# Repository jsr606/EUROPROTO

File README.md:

# EUROPROTO
an arduino / atmega platform for making digital eurorack modules and
various helper PCBs

based on on the [CHEAP, FAT and OPEN](https://vsionhairies.info/) synthesizer

## a what?
arduino based eurorack module with dual channel DAC output

kind of works :)

this is a prototyping platform. you can make modules that looks like this

## first version for sound days at MPLab
[workshop description and assembly guides here](/SoundDays_MPlab/README.md)

## rev3 board is here now
look in the rev3 folder. it's all old eagle stuff that i can't really open anymore, but it should possibly work?

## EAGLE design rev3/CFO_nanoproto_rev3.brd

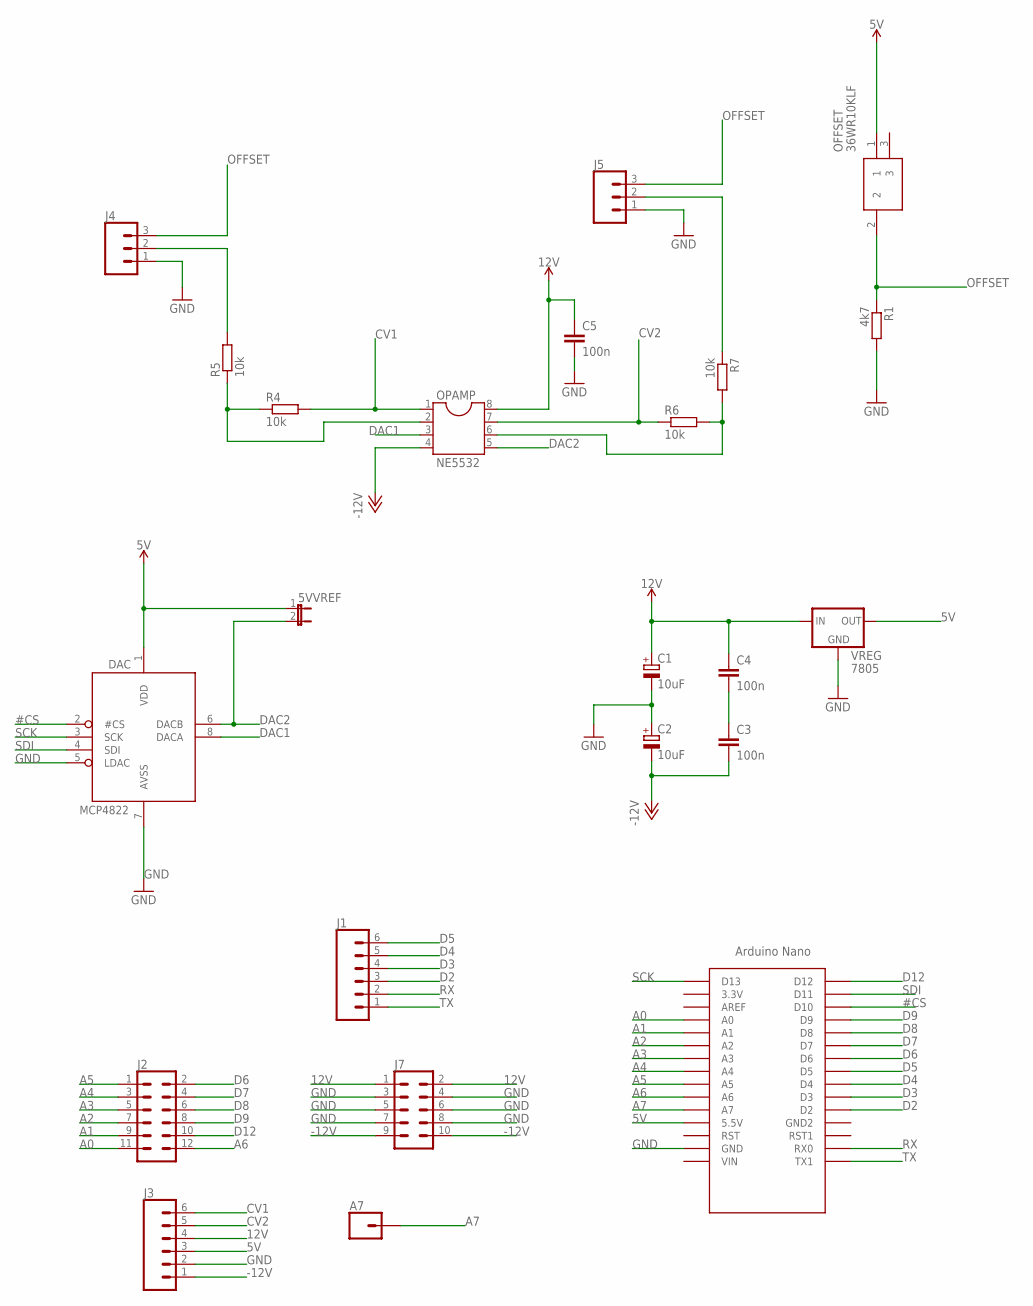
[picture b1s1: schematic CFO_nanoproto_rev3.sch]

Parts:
5VVREF: JUMPER-2PTH; 1X02
A7: CONN_01; 1X01
C1, C2: 10uF; E2-5
C3, C4, C5: 100n; C050-025X075
DAC: MCP4822; DIL08
J1, J3: CONN_06NO_SILK_NO_POP; 1X06_NO_SILK
J2: 2X6 FEMALE; 2X6
J4, J5: CONN_03; 1X03
J7: EURO_CONN_05X2SHD; 2X5-SHROUDED
OFFSET: 36WR10KLF
OPAMP: NE5532; DIL08
R1: 4k7; 0207/10
R4, R5, R6, R7: 10k; 0207/10
U$2: NANO
VREG: 7805; 78XXL_NOHOLE

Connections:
5V: 5VVREF.1, DAC.1 (VDD), J3.3, OFFSET.1, U$2.5V (5.5V), VREG.OUT
12V: C1.+, C4.1, C5.1, J3.4, J7.1, J7.2, OPAMP.8, VREG.IN
#CS: DAC.2 (#CS), U$2.D10
-12V: C2.-, C3.2, J3.1, J7.9, J7.10, OPAMP.4
A0: J2.11, U$2.A0
A1: J2.9, U$2.A1
A2: J2.7, U$2.A2
A3: J2.5, U$2.A3
A4: J2.3, U$2.A4
A5: J2.1, U$2.A5
A6: J2.12, U$2.A6
A7: A7.1, U$2.A7
CV1: J3.6, OPAMP.1, R4.2
CV2: J3.5, OPAMP.7, R6.1
D2: J1.3, U$2.D2
D3: J1.4, U$2.D3
D4: J1.5, U$2.D4
D5: J1.6, U$2.D5
D6: J2.2, U$2.D6
D7: J2.4, U$2.D7
D8: J2.6, U$2.D8
D9: J2.8, U$2.D9
D12: J2.10, U$2.D12
DAC1: DAC.8 (DACA), OPAMP.3
DAC2: 5VVREF.2, DAC.6 (DACB), OPAMP.5
GND: C1.-, C2.+, C5.2, DAC.5 (LDAC), DAC.7 (AVSS), J3.2, J4.1, J5.1, J7.3, J7.4, J7.5, J7.6, J7.7, J7.8, R1.2, U$2.GND, VREG.GND
unnamed: C3.1, C4.2
unnamed: OPAMP.6, R6.2, R7.2
unnamed: J4.2, R5.2
unnamed: OPAMP.2, R4.1, R5.1
unnamed: J5.2, R7.1
OFFSET: J4.3, J5.3, OFFSET.2, R1.1
RX: J1.2, U$2.RX0
SCK: DAC.3 (SCK), U$2.D13
SDI: DAC.4 (SDI), U$2.D11
TX: J1.1, U$2.TX1

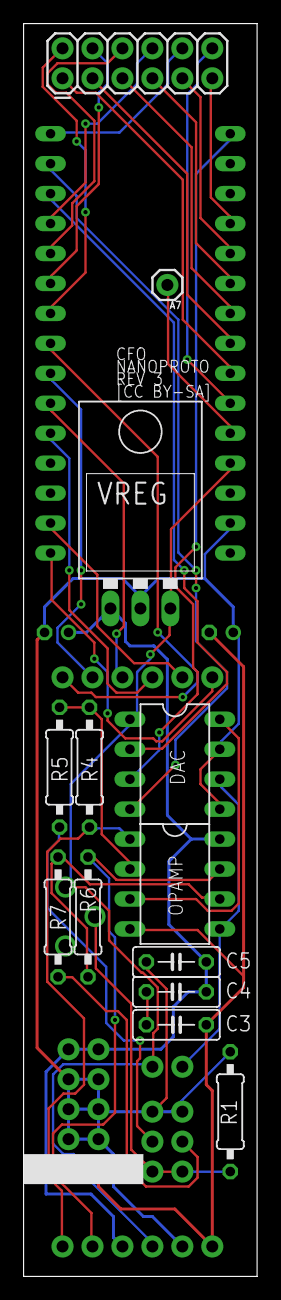
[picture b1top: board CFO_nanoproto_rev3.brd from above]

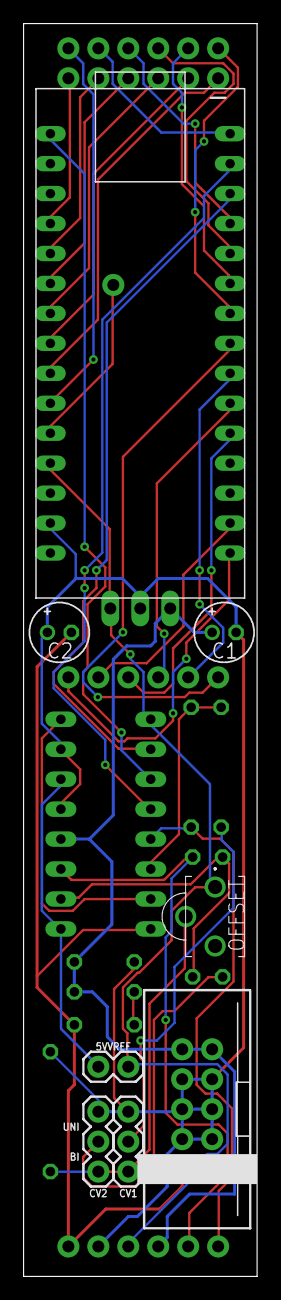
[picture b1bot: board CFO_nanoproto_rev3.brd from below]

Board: 2 copper layers, 19.8 x 106.2 mm, 23 parts (8 on the bottom side), 36 nets.

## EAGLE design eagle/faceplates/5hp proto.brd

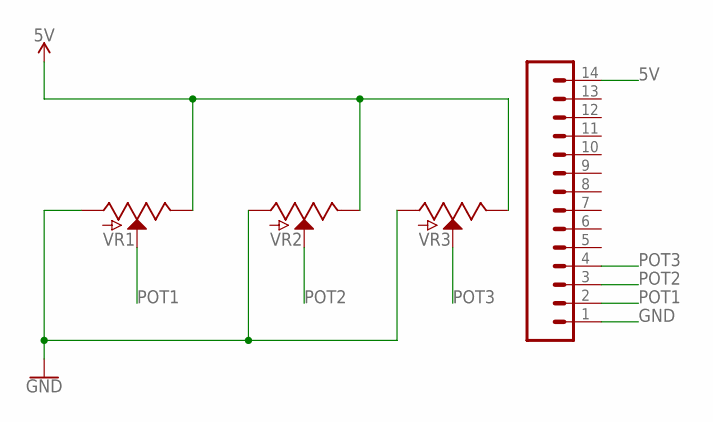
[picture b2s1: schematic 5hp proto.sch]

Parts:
J2: CONN_14SQUARE; 1X14
VR1, VR2, VR3: POTENTIOMETERPOTV; POT_V

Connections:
5V: J2.14, VR1.P3 (E), VR2.P3 (E), VR3.P3 (E)
GND: J2.1, VR1.P1 (A), VR2.P1 (A), VR3.P1 (A)
POT1: J2.2, VR1.P2 (S)
POT2: J2.3, VR2.P2 (S)
POT3: J2.4, VR3.P2 (S)

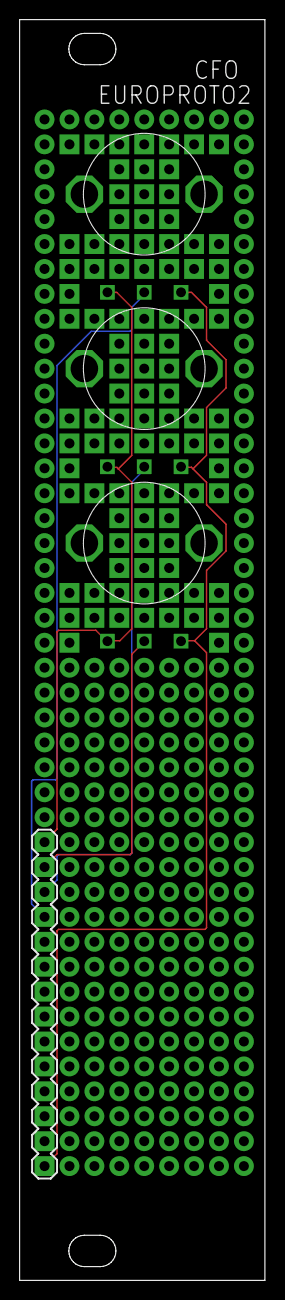
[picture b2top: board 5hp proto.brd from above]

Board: 2 copper layers, 25.0 x 128.5 mm, 4 parts (0 on the bottom side), 5 nets.

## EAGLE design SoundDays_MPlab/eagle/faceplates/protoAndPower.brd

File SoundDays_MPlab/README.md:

# CFO EUROPROTO 1
# digital modular

workshop participants will learn to prototype simple arduino based modules that can interact with the eurorack modular world.  

programming microcontrollers in eurorack format, brings a dirty, cheap and flexible hacking approach to eurorack modular. by introducing programmable digital utility modules in the modular world we open up a pandoras box of algorithmic composition and wonderful glitches.  

the outcome of the workshop will be true hybrid modular systems that is self playing and self modulating. saturday night the workshop participants will gather for a massive common patch jam based on produced modules and doepfer a-100 system which is already available for us in mplab.  

http://sound.mplab.lv/workshops/jacob-remin/  
jacob remin, liepaja, 2-5 may 2019

## teachers

jacob remin & reinis nalivaiko

## links / references

https://vsionhairies.info/  
http://www.jacobremin.com/  
https://www.arduino.cc/  
http://sound.mplab.lv/  

## thanks!

erica synths  
https://www.ericasynths.lv/  
nordic culture point  
https://www.nordiskkulturkontakt.org  

## more infos

[build instructions](https://github.com/jsr606/EUROPROTO/tree/master/SoundDays_MPlab/build_instructions)

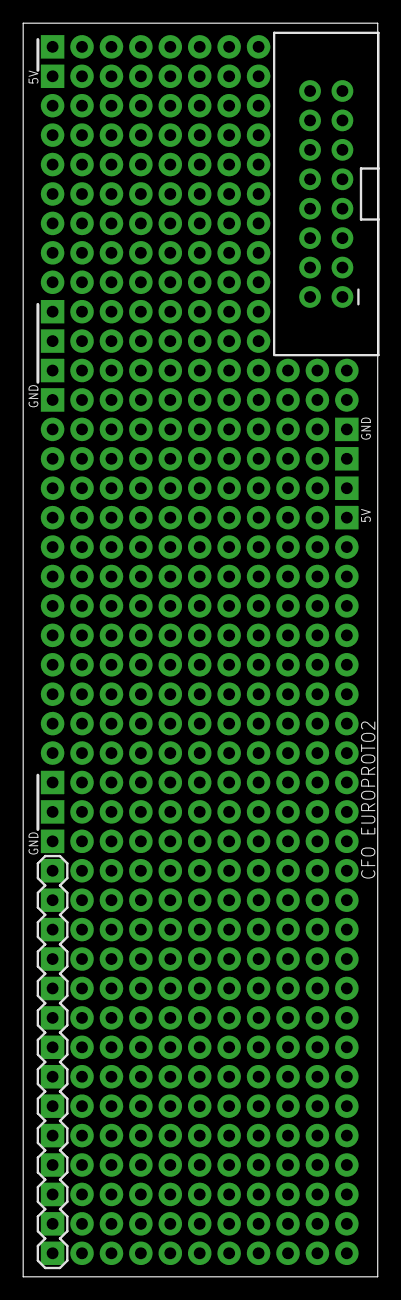
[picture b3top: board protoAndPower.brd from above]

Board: 2 copper layers, 30.6 x 108.2 mm, 12 parts (0 on the bottom side), 6 nets, no tracks yet.

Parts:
J1: 1X04
J2: 1X14
J3: 2X8-SHROUDED_LOCK
J4, J5, J28, J29, J31, J34, J37, J39, J42: 1X01

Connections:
5V: J1.4, J2.14, J3.11, J3.12, J4.1, J5.1
12V: J3.9, J3.10
CV: J3.13, J3.14
GATE: J3.15, J3.16
GND: J1.1, J2.1, J3.3, J3.4, J3.5, J3.6, J3.7, J3.8, J28.1, J29.1, J31.1, J34.1, J37.1, J39.1, J42.1
VEE: J3.1, J3.2

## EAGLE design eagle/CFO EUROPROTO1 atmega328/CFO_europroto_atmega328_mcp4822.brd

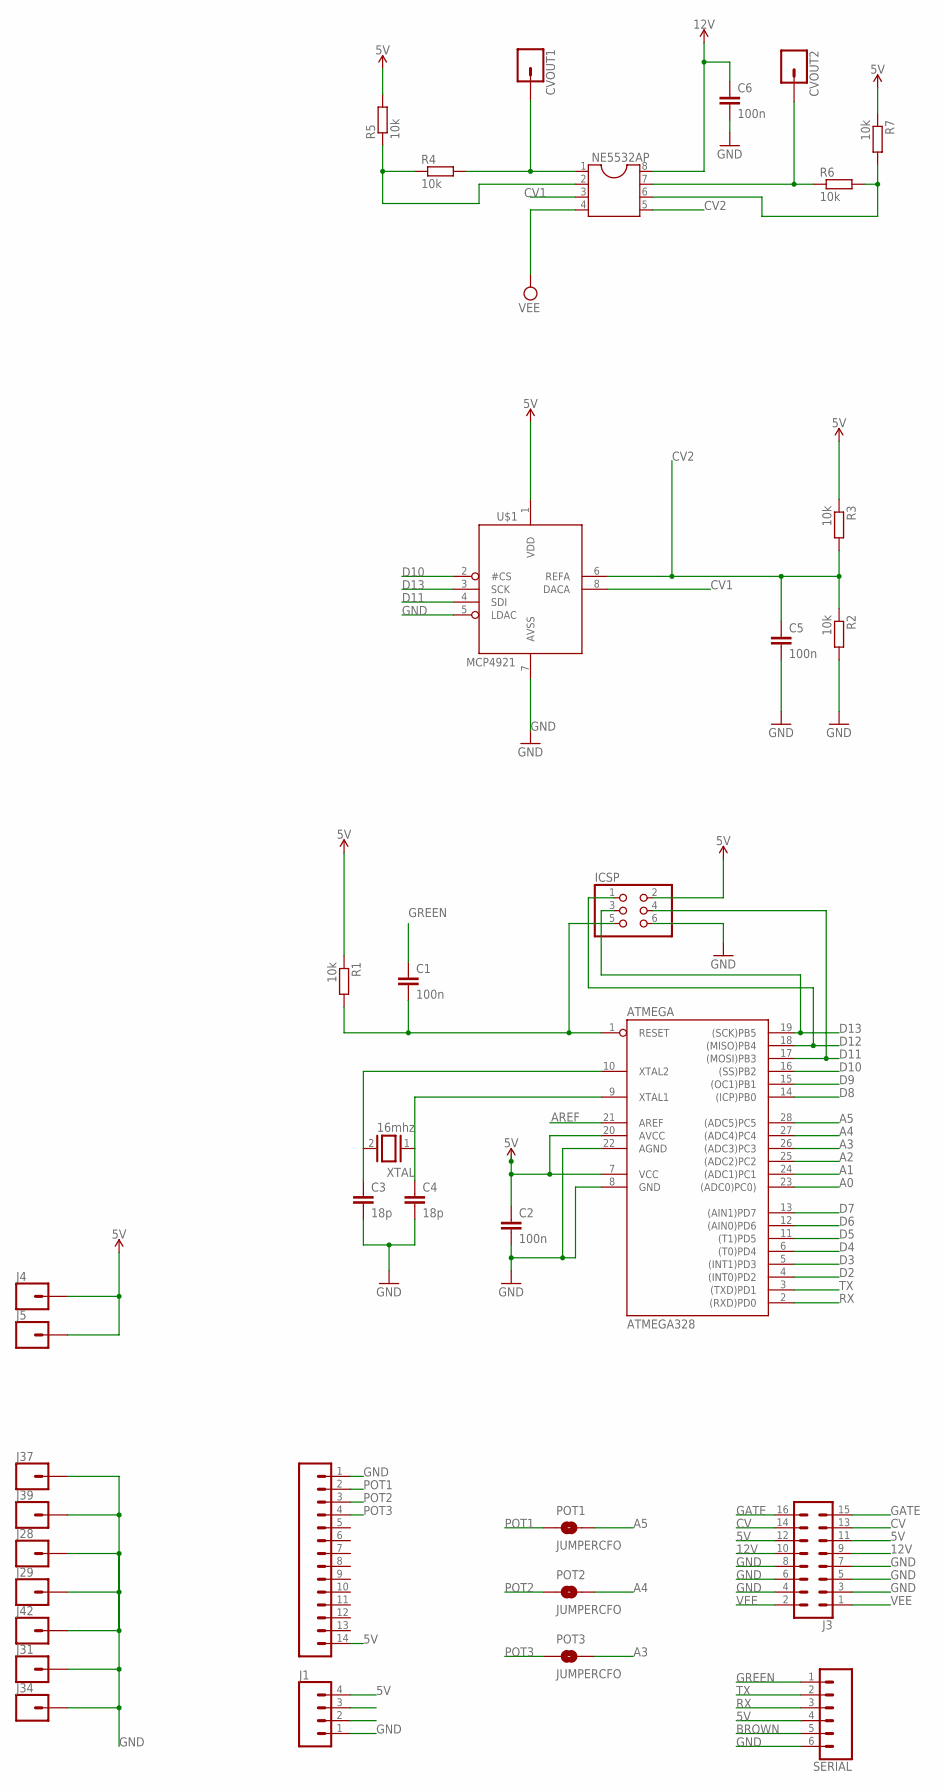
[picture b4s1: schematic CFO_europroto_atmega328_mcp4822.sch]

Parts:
ATMEGA: ATMEGA328; DIL28-3
C1, C2, C5, C6: 100n; C050-025X075
C3, C4: 18p; C050-025X075
CVOUT1, CVOUT2: CONN_01; 1X01
ICSP: PINHD-2X3; 2X03
J1: CONN_04; 1X04
J2: CONN_14SQUARE; 1X14
J3: CONN_08X2_SHROUD; 2X8-SHROUDED_LOCK
J4, J5, J28, J29, J31, J34, J37, J39, J42: CONN_01; 1X01
NE5532AP: DIL8; DIL08
POT1, POT2, POT3: JUMPERCFO; SMT-JUMPER_2_NO_NO-SILK_ROUND
R1, R2, R3, R4, R5, R6, R7: 10k; 0207/10
SERIAL: CONN_06SILK_FEMALE_PTH; 1X06
U$1: MCP4921; DIL08
XTAL: 16mhz; QS

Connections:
5V: ATMEGA.7 (VCC), ATMEGA.20 (AVCC), C2.1, ICSP.2, J1.4, J2.14, J3.11, J3.12, J4.1, J5.1, R1.1, R3.1, R5.2, R7.1, SERIAL.4, U$1.1 (VDD)
12V: C6.1, J3.9, J3.10, NE5532AP.8
A0: ATMEGA.23 ((ADC0)PC0))
A1: ATMEGA.24 ((ADC1)PC1)
A2: ATMEGA.25 ((ADC2)PC2)
A3: ATMEGA.26 ((ADC3)PC3), POT3.2
A4: ATMEGA.27 ((ADC4)PC4), POT2.2
A5: ATMEGA.28 ((ADC5)PC5), POT1.2
AREF: ATMEGA.21 (AREF)
BROWN: SERIAL.5
CV: J3.13, J3.14
CV1: NE5532AP.3, U$1.8 (DACA)
CV2: C5.1, NE5532AP.5, R2.1, R3.2, U$1.6 (REFA)
CVOUT1: CVOUT1.1, NE5532AP.1, R4.2
CVOUT2: CVOUT2.1, NE5532AP.7, R6.1
D2: ATMEGA.4 ((INT0)PD2)
D3: ATMEGA.5 ((INT1)PD3)
D4: ATMEGA.6 ((T0)PD4)
D5: ATMEGA.11 ((T1)PD5)
D6: ATMEGA.12 ((AIN0)PD6)
D7: ATMEGA.13 ((AIN1)PD7)
D8: ATMEGA.14 ((ICP)PB0)
D9: ATMEGA.15 ((OC1)PB1)
D10: ATMEGA.16 ((SS)PB2), U$1.2 (#CS)
D11: ATMEGA.17 ((MOSI)PB3), ICSP.4, U$1.4 (SDI)
D12: ATMEGA.18 ((MISO)PB4), ICSP.1
D13: ATMEGA.19 ((SCK)PB5), ICSP.3, U$1.3 (SCK)
GATE: J3.15, J3.16
GND: ATMEGA.8 (GND), ATMEGA.22 (AGND), C2.2, C3.2, C4.2, C5.2, C6.2, ICSP.6, J1.1, J2.1, J3.3, J3.4, J3.5, J3.6, J3.7, J3.8, J28.1, J29.1, J31.1, J34.1, J37.1, J39.1, J42.1, R2.2, SERIAL.6, U$1.5 (LDAC), U$1.7 (AVSS)
GREEN: C1.1, SERIAL.1
unnamed: ATMEGA.10 (XTAL2), C3.1, XTAL.2
unnamed: NE5532AP.6, R6.2, R7.2
unnamed: NE5532AP.2, R4.1, R5.1
unnamed: ATMEGA.9 (XTAL1), C4.1, XTAL.1
POT1: J2.2, POT1.1
POT2: J2.3, POT2.1
POT3: J2.4, POT3.1
RESET: ATMEGA.1 (RESET), C1.2, ICSP.5, R1.2
RX: ATMEGA.2 ((RXD)PD0), SERIAL.3
TX: ATMEGA.3 ((TXD)PD1), SERIAL.2
VEE: J3.1, J3.2, NE5532AP.4

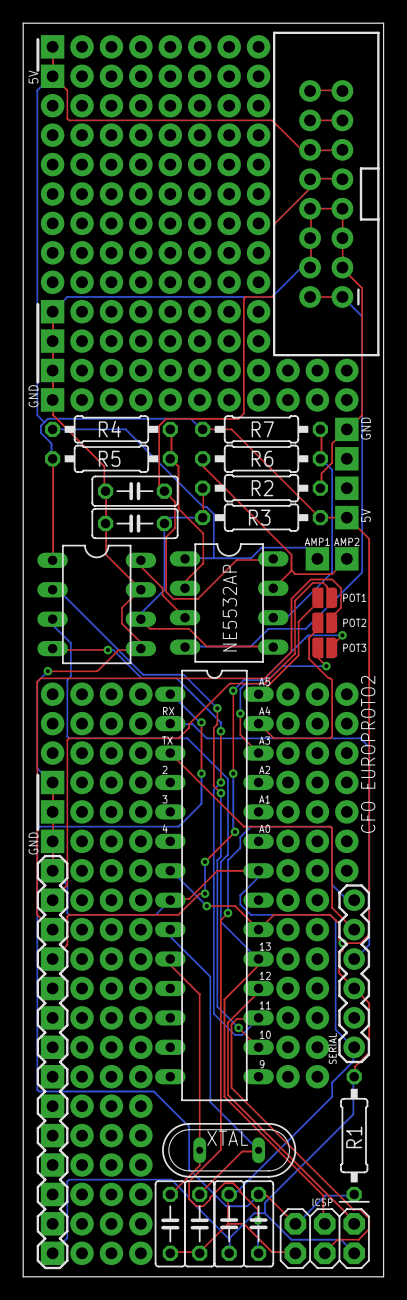
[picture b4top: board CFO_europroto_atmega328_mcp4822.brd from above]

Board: 2 copper layers, 31.1 x 108.2 mm, 36 parts (0 on the bottom side), 28 nets.

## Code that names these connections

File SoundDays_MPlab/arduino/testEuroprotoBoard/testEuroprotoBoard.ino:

#include <SPI.h>
#include <DAC_MCP49xx.h>

#define SS_PIN 10 // slave select / chip select
DAC_MCP49xx dac(DAC_MCP49xx::MCP4921, SS_PIN);

// NB: pins used by DAC: 10, 11, 13

int pot1 = A3, pot2 = A4, pot3 = A5;

int counter = 0;

void setup() {
  // setup DAC
  dac.setSPIDivider(SPI_CLOCK_DIV16);
  dac.setPortWrite(true);
  dac.setGain(2);
  
  Serial.begin(115200);
}

void loop() {
  int p1 = analogRead(pot1);
  int p2 = analogRead(pot2);
  int p3 = analogRead(pot3);
  Serial.print(p1);
  Serial.print("\t");
  Serial.print(p2);
  Serial.print("\t");
  Serial.print(p3);
  Serial.print("\t");
  Serial.println();
  
  dac.output(counter); // dac is 12 bit: 0-4095, analogRead is 10 bit: 0-1023
  counter++;
  counter = counter % 4096;
  
  delay(20);
}

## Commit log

2019-05-02 build instructions added
2019-05-02 fix images
2019-05-02 spelling etc
2019-05-02 links_folders
2019-05-02 folders names
2019-05-02 add image
2019-05-02 add schedule
2019-05-02 BOM / schedule
2019-05-02 added pics
2019-05-03 added oscillator code
2019-05-03 programming
2019-05-03 split build and code
2019-05-03 added atmega pinout pic
2019-05-03 updated atmega328 pic
2019-05-03 folder structure
2019-05-03 pics
2019-05-03 pics / photos
2019-05-03 drill
2019-05-03 connectGND
2019-05-03 added pic
2019-05-03 CV in
2019-05-03 arduino and programmers
2019-05-03 add MCP49xx library
2019-05-03 settings.png
2019-05-06 Oscillator with CV Input
    An oscillator with CV Input written during Sound Days.
2019-05-27 added eagle files
2019-05-27 added schematic screenshot from eagle
2019-05-30 added MCP4822 example
2019-06-01 added op amp circuit simulation
2019-06-01 added CV input scaling simulation link and screenshot
2019-06-05 alternative op amp circuit
2019-06-19 fix vref level on mcp4921 and added possibility of CV range toggle
2019-06-19 amp pad 1 and 2 flipped
2025-01-21 added rev3
2025-01-21 added rev3 and README.md

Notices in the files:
rev3/CFO_nanoproto_rev3.brd:
[CC BY-SA]
parts and their libraries:
SparkFun-Connectors: Licensing: Creative Commons ShareAlike 4.0 International - https://creativecommons.org/licenses/by-sa/4.0
